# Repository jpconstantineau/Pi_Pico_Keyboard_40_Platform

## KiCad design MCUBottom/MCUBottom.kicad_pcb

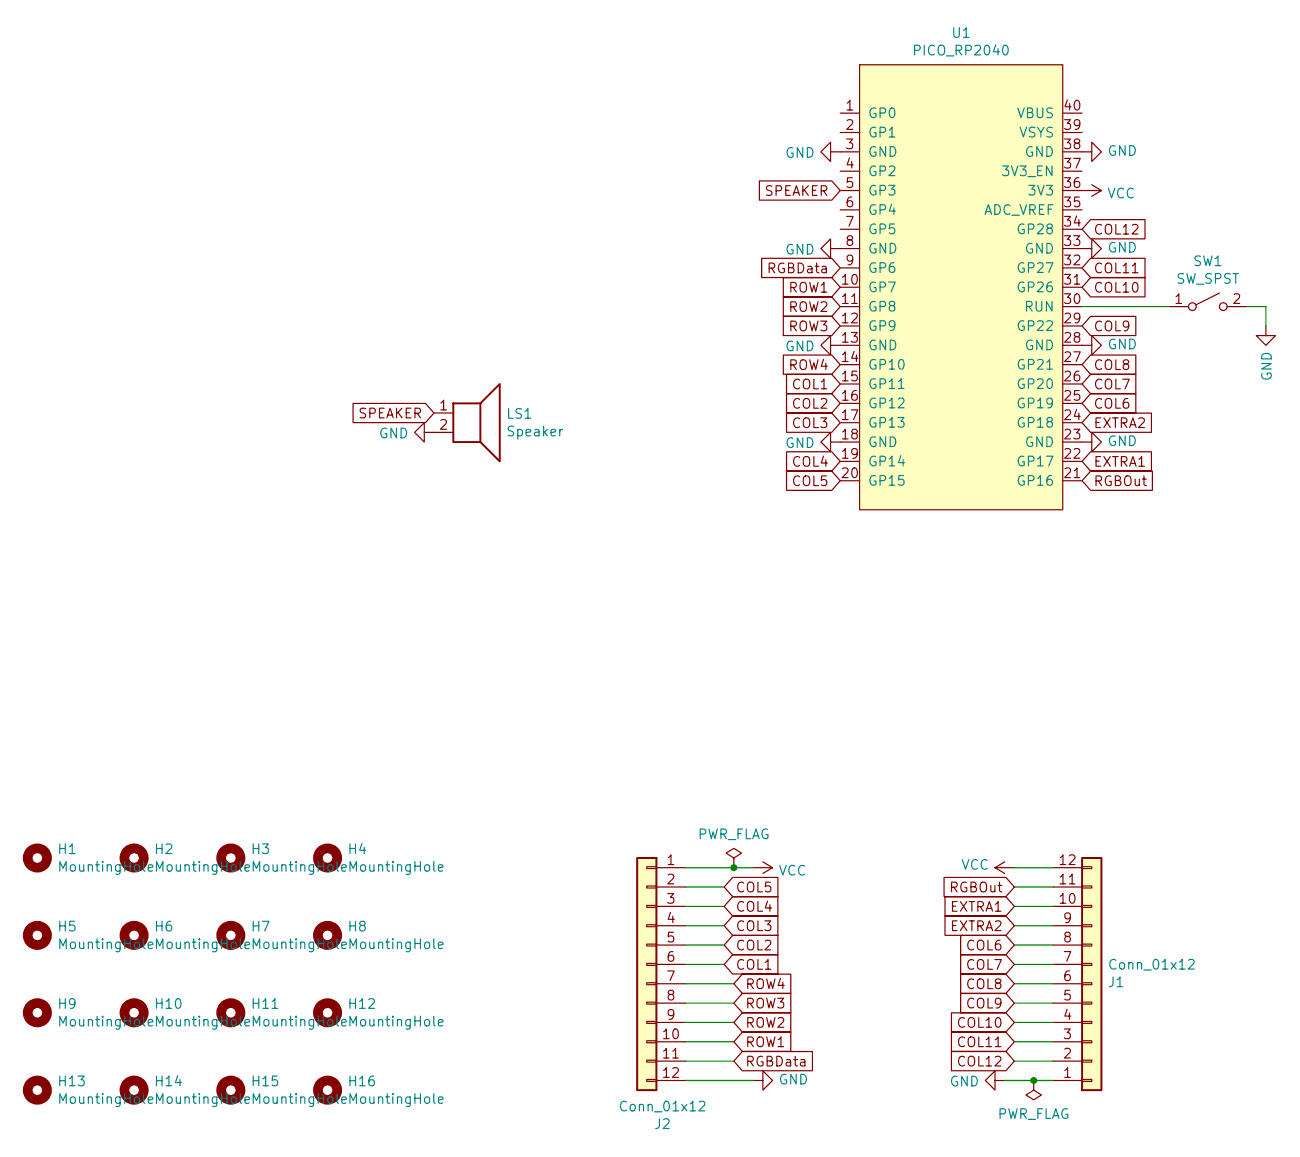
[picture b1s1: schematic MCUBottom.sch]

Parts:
H1, H2, H3, H4, H5, H6, H7, H8, H9, H10, H11, H12, H13, H14, H15, H16: MountingHole; MountingHole_2.2mm_M2
J1, J2: Conn_01x12; JUSHUO-AFC07-S12FCC-00_C11051_1x12-1MP_P0.50mm_Horizontal
LS1: Speaker; Buzzer_Mallory_AST1109MLTRQ
SW1: SW_SPST; Panasonic_EVQPUJ_EVQPUA
U1: PICO_RP2040; RPi_Pico_SMD_TH

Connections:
COL1: J2.6, U1.15 (GP11)
COL2: J2.5, U1.16 (GP12)
COL3: J2.4, U1.17 (GP13)
COL4: J2.3, U1.19 (GP14)
COL5: J2.2, U1.20 (GP15)
COL6: J1.8, U1.25 (GP19)
COL7: J1.7, U1.26 (GP20)
COL8: J1.6, U1.27 (GP21)
COL9: J1.5, U1.29 (GP22)
COL10: J1.4, U1.31 (GP26)
COL11: J1.3, U1.32 (GP27)
COL12: J1.2, U1.34 (GP28)
EXTRA1: J1.10, U1.22 (GP17)
EXTRA2: J1.9, U1.24 (GP18)
GND: J1.1, J2.12, LS1.2, SW1.2 (B), U1.3 (GND), U1.8 (GND), U1.13 (GND), U1.18 (GND), U1.23 (GND), U1.28 (GND), U1.33 (GND), U1.38 (GND)
unnamed: SW1.1 (A), U1.30 (RUN)
RGBData: J2.11, U1.9 (GP6)
RGBOut: J1.11, U1.21 (GP16)
ROW1: J2.10, U1.10 (GP7)
ROW2: J2.9, U1.11 (GP8)
ROW3: J2.8, U1.12 (GP9)
ROW4: J2.7, U1.14 (GP10)
SPEAKER: LS1.1, U1.5 (GP3)
VCC: J1.12, J2.1, U1.36 (3V3)

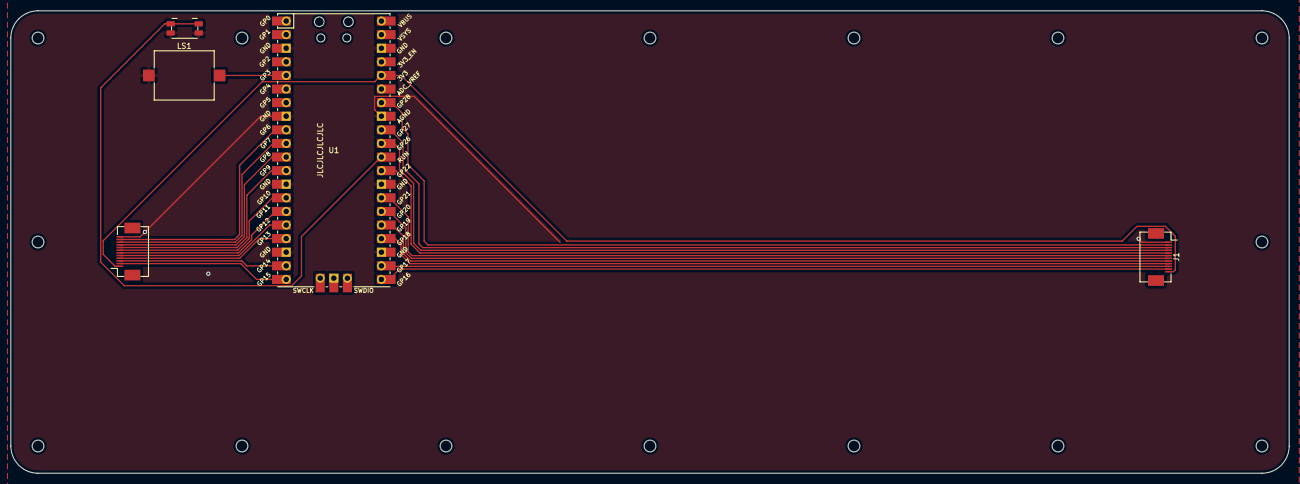
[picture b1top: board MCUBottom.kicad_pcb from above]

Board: 2 copper layers, 238.8 x 86.4 mm, 21 parts (0 on the bottom side), 24 nets.

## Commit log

2021-09-20 initial PCBs
